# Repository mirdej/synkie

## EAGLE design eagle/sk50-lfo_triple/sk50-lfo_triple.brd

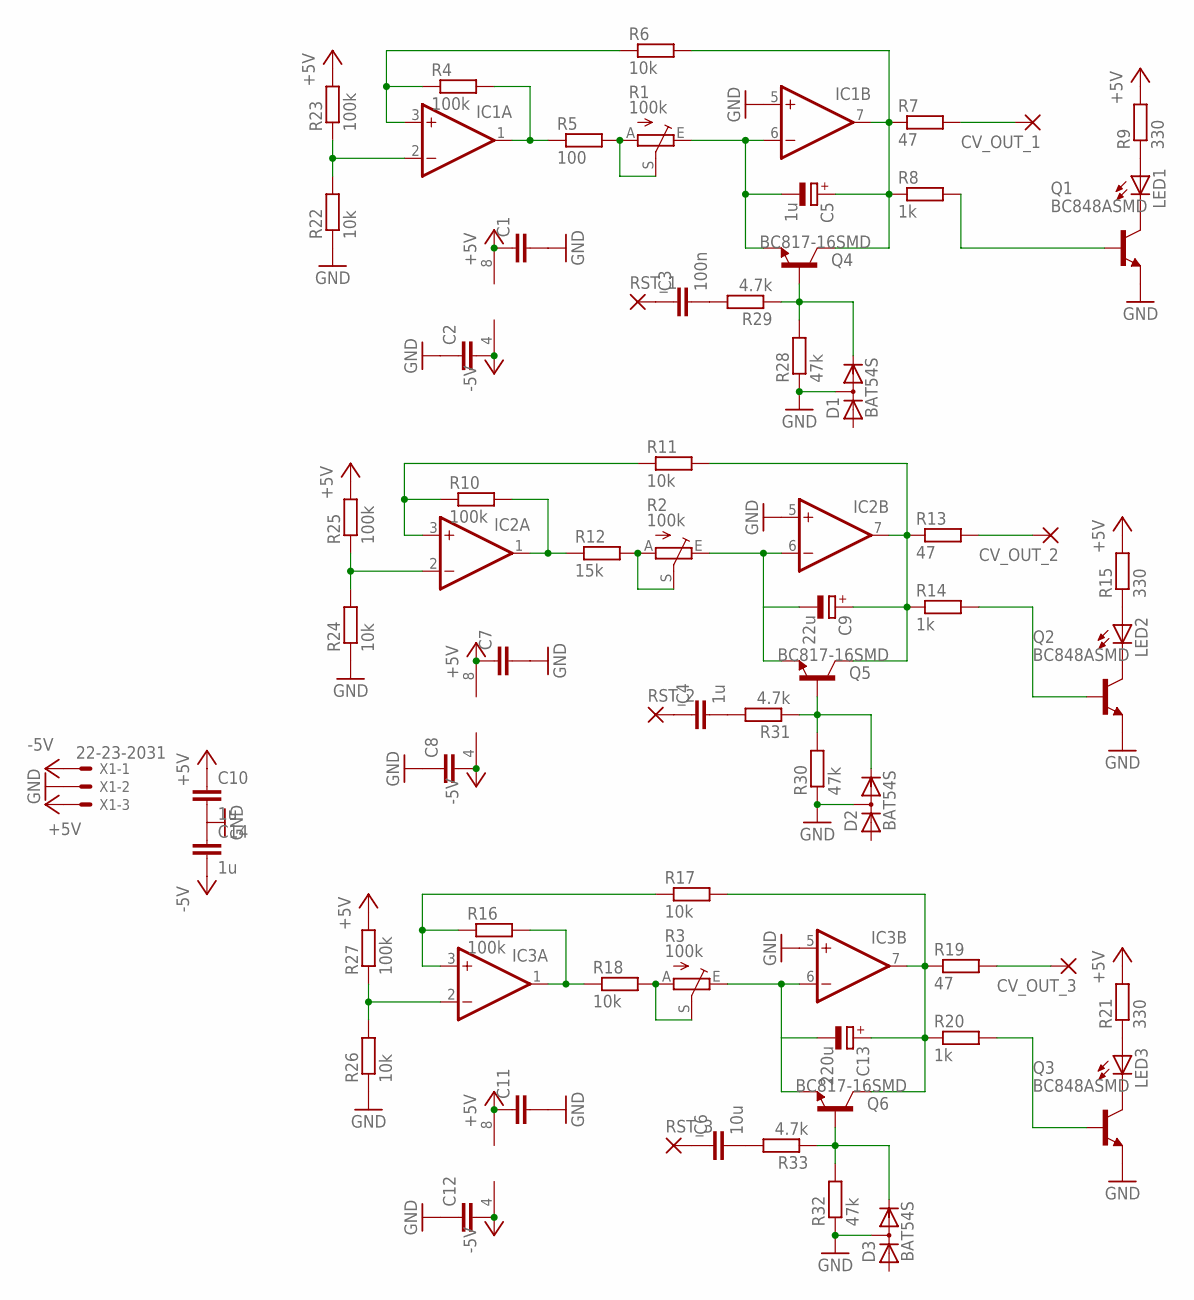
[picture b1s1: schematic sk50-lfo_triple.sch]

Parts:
C1, C2, C7, C8, C11, C12: C-EUC1206; C1206
C3: 100n; C1206
C4, C10, C14: 1u; C1206
C5: 1u; E2,5-5
C6: 10u; C1206
C9: 22u; E2,5-5
C13: 220u; E2,5-5
CV_OUT_1, CV_OUT_2, CV_OUT_3: 3,17/1,1
D1, D2, D3: BAT54S; SOT23
IC1, IC2, IC3: 2AMP_P8+4D; SO08
LED1, LED2, LED3: LED3MM
Q1, Q2, Q3: BC848ASMD; SOT23
Q4, Q5, Q6: BC817-16SMD; SOT23-BEC
R1, R2, R3: 100k; CIP20C-6MM
R4, R10, R16, R23, R25, R27: 100k; R1206
R5: 100; R1206
R6, R11, R17, R18, R22, R24, R26: 10k; R1206
R7, R13, R19: 47; R1206
R8, R14, R20: 1k; R1206
R9, R15, R21: 330; R1206
R12: 15k; R1206
R28, R30, R32: 47k; R1206
R29, R31, R33: 4.7k; R1206
RST_1, RST_2, RST_3: 3,17/1,1
X1: 22-23-2031

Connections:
+5V: C1.1, C7.1, C10.1, C11.1, IC1.8 (V+), IC2.8 (V+), IC3.8 (V+), R9.2, R15.2, R21.2, R23.2, R25.2, R27.2, X1.3
-5V: C2.2, C8.2, C12.2, C14.2, IC1.4 (V-), IC2.4 (V-), IC3.4 (V-), X1.1
GND: C1.2, C2.1, C7.2, C8.1, C10.2, C11.2, C12.1, C14.1, D1.3 (AC), D2.3 (AC), D3.3 (AC), IC1.5 (+IN), IC2.5 (+IN), IC3.5 (+IN), Q1.2 (E), Q2.2 (E), Q3.2 (E), R22.1, R24.1, R26.1, R28.1, R30.1, R32.1, X1.2
unnamed: IC1.3 (+IN), R4.1, R6.1
unnamed: IC1.1 (OUT), R4.2, R5.1
unnamed: R1.A, R1.S, R5.2
unnamed: C5.-, IC1.6 (-IN), Q4.E, R1.E
unnamed: C5.+, IC1.7 (OUT), Q4.C, R6.2, R7.1, R8.1
unnamed: LED2.A, R15.1
unnamed: CV_OUT_1.1, R7.2
unnamed: Q1.1 (B), R8.2
unnamed: LED1.A, R9.1
unnamed: LED1.K (C), Q1.3 (C)
unnamed: IC2.3 (+IN), R10.1, R11.1
unnamed: IC2.1 (OUT), R10.2, R12.1
unnamed: R2.A, R2.S, R12.2
unnamed: C9.-, IC2.6 (-IN), Q5.E, R2.E
unnamed: C9.+, IC2.7 (OUT), Q5.C, R11.2, R13.1, R14.1
unnamed: LED2.K (C), Q2.3 (C)
unnamed: CV_OUT_2.1, R13.2
unnamed: Q2.1 (B), R14.2
unnamed: LED3.A, R21.1
unnamed: LED3.K (C), Q3.3 (C)
unnamed: IC3.3 (+IN), R16.1, R17.1
unnamed: IC3.1 (OUT), R16.2, R18.1
unnamed: R3.A, R3.S, R18.2
unnamed: C13.-, IC3.6 (-IN), Q6.E, R3.E
unnamed: C13.+, IC3.7 (OUT), Q6.C, R17.2, R19.1, R20.1
unnamed: Q3.1 (B), R20.2
unnamed: CV_OUT_3.1, R19.2
unnamed: IC1.2 (-IN), R22.2, R23.1
unnamed: IC2.2 (-IN), R24.2, R25.1
unnamed: IC3.2 (-IN), R26.2, R27.1
unnamed: C3.2, R29.2
unnamed: C3.1, RST_1.1
unnamed: D2.2 (C), Q5.B, R30.2, R31.1
unnamed: D1.2 (C), Q4.B, R28.2, R29.1
unnamed: C4.2, R31.2
unnamed: C6.2, R33.2
unnamed: C4.1, RST_2.1
unnamed: C6.1, RST_3.1
unnamed: D3.2 (C), Q6.B, R32.2, R33.1

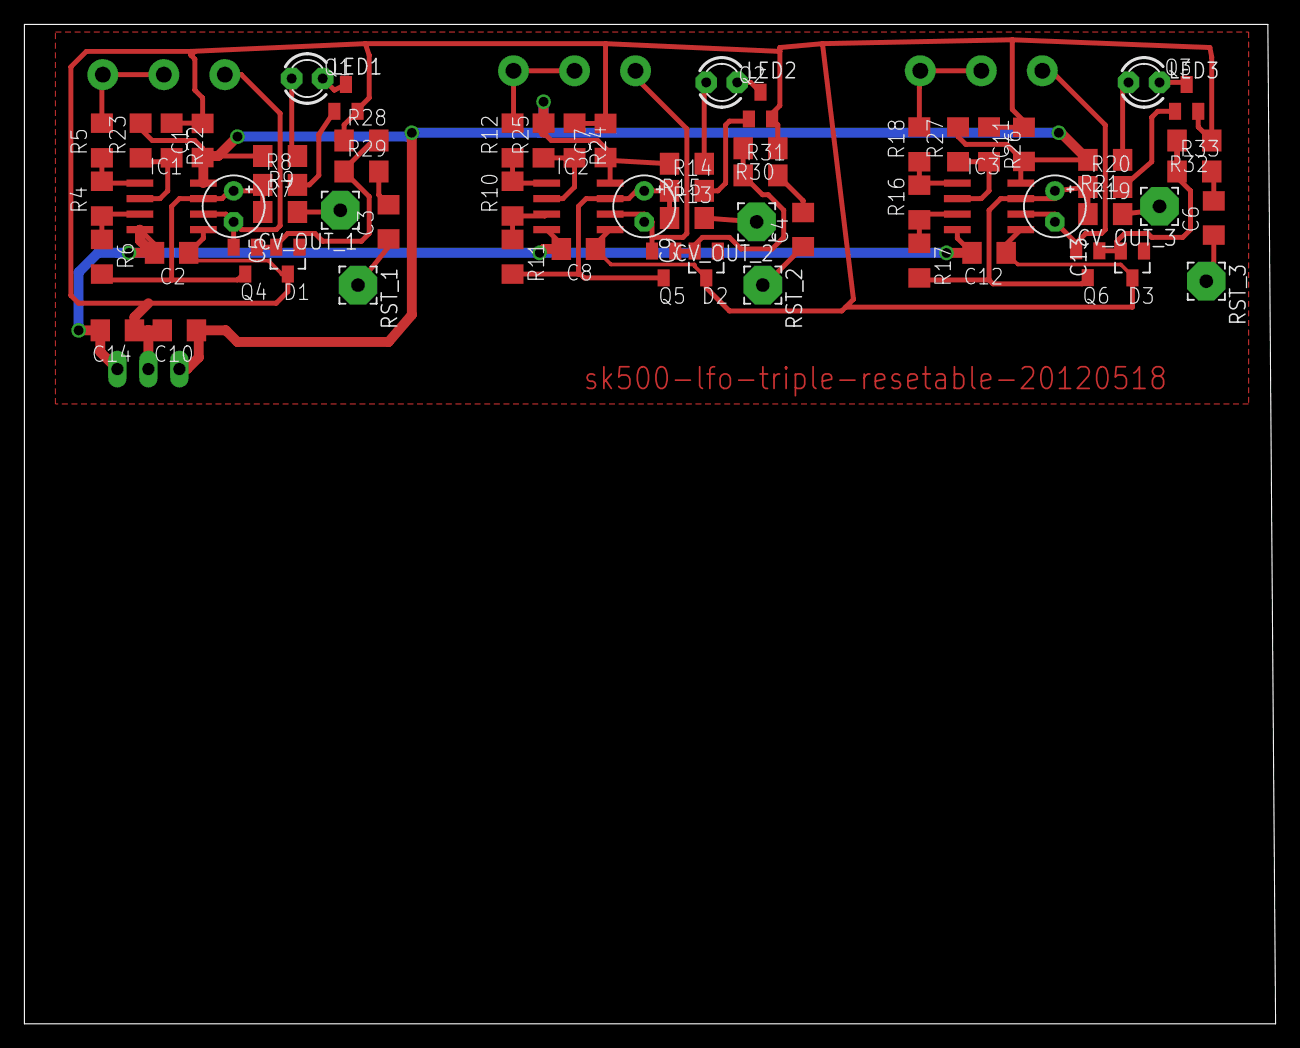
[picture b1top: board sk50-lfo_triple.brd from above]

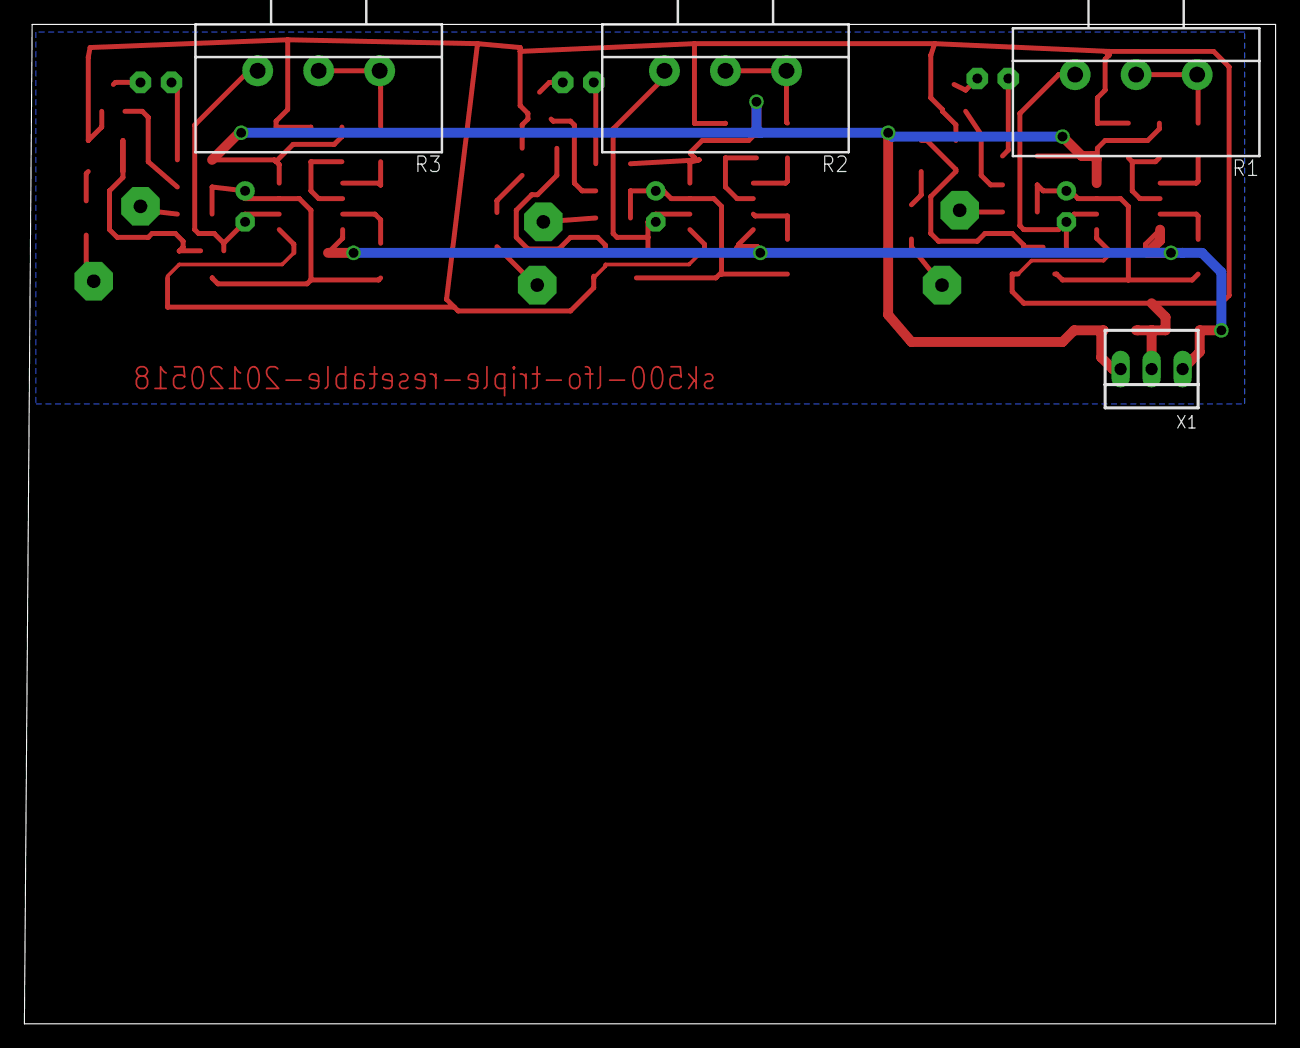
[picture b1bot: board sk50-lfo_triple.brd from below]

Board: 2 copper layers, 102.5 x 81.9 mm, 69 parts (4 on the bottom side), 42 nets.

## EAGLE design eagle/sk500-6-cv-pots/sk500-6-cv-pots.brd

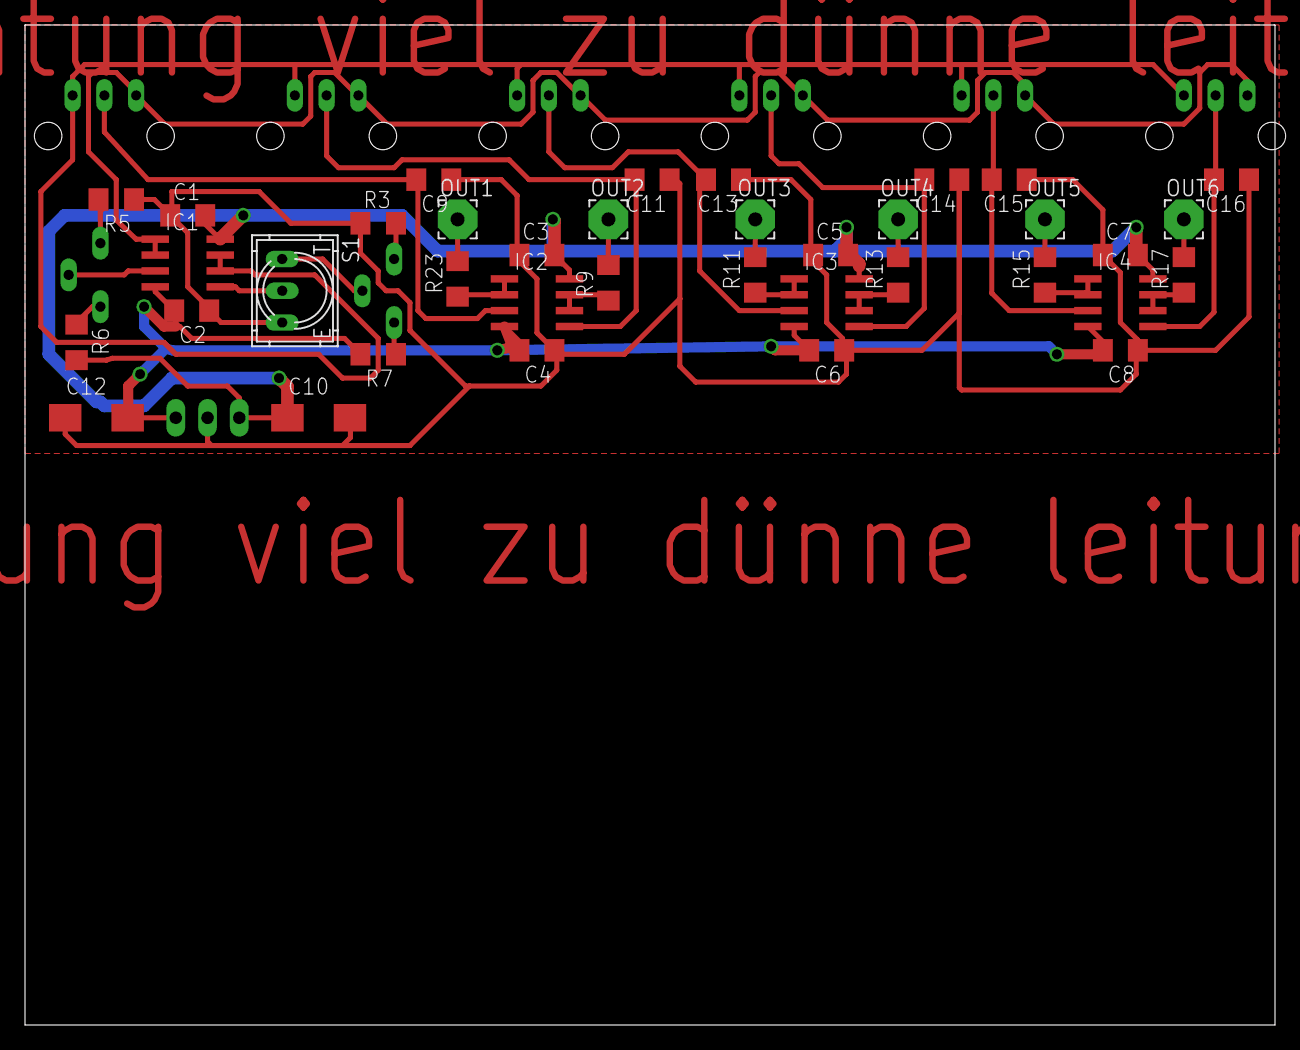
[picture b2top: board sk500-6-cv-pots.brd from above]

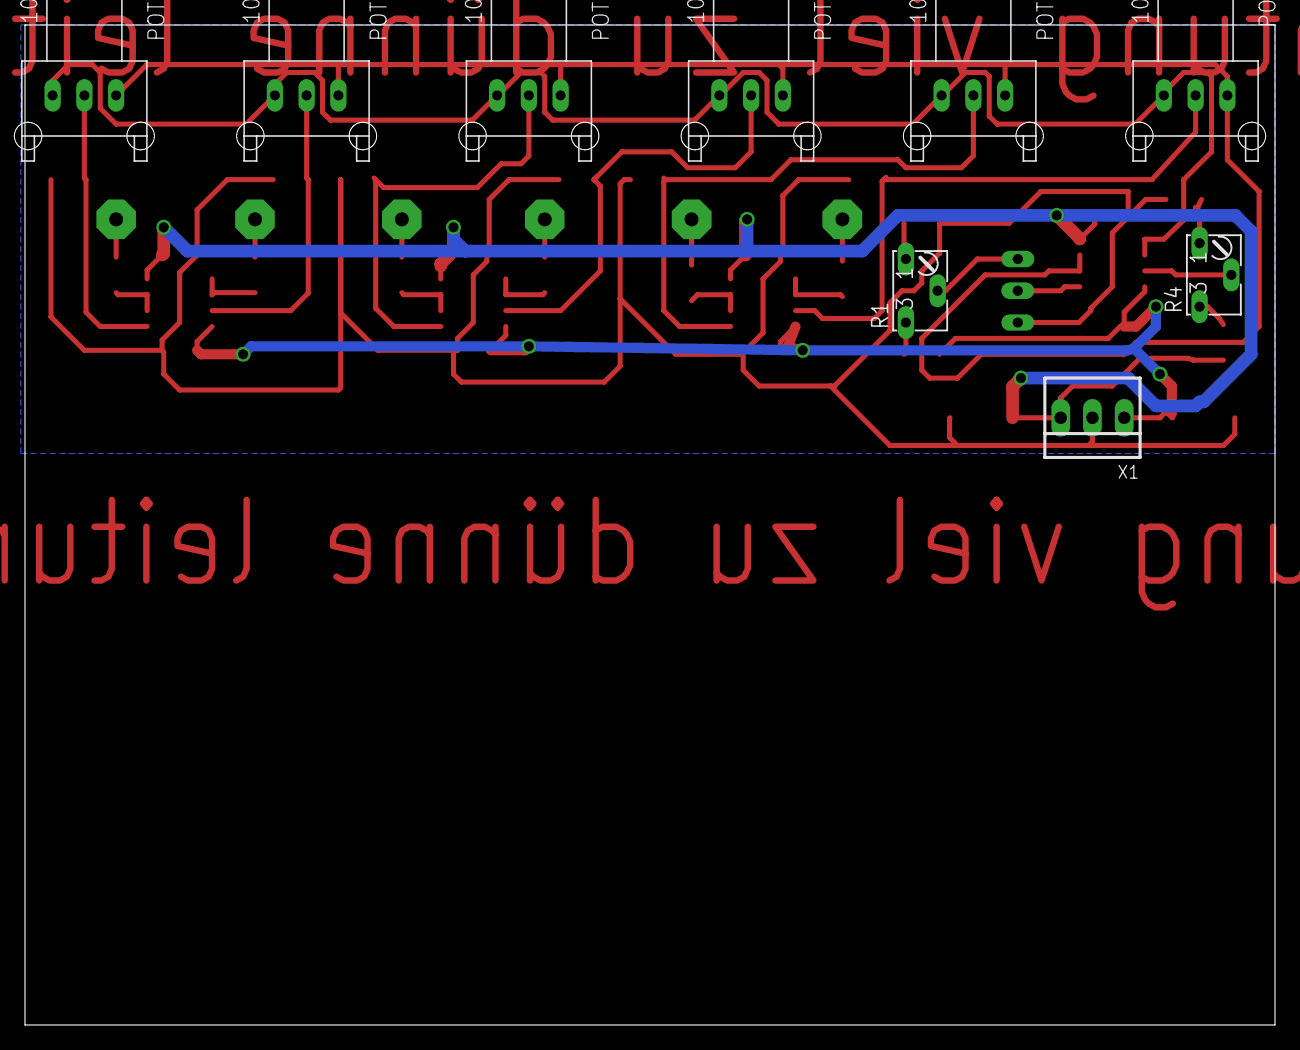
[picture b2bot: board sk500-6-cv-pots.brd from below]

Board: 2 copper layers, 100.0 x 80.0 mm, 46 parts (9 on the bottom side), 30 nets.

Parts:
C1, C2, C3, C4, C5, C6, C7, C8, C9, C11, C13, C14, C15, C16: C1206
C10, C12: CT6032
IC1, IC2, IC3, IC4: LM833D; SO08
OUT1, OUT2, OUT3, OUT4, OUT5, OUT6: 3,17/1,1
POT10K, POT10K1, POT10K2, POT10K3, POT10K4, POT10K5: 10k; ALPS_RK09K111_H
R1, R4: 500; B64W
R3, R5: 330; R1206
R6, R7: 1k6; R1206
R9, R11, R13, R15, R17, R23: 75; R1206
S1: 9077-1
X1: 22-23-2031

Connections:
+5V: C1.2, C3.2, C5.2, C7.2, C10.+, IC1.8, IC2.8, IC3.8, IC4.8, R6.2, X1.3
-5V: C2.2, C4.2, C6.2, C8.2, C12.-, IC1.4, IC2.4, IC3.4, IC4.4, R7.2, X1.1
GND: C1.1, C2.1, C3.1, C4.1, C5.1, C6.1, C7.1, C8.1, C9.1, C10.-, C11.1, C12.+, C13.1, C14.1, C15.1, C16.1, R3.1, R5.1, S1.3, X1.2
unnamed: IC1.5, S1.2
unnamed: C9.2, IC2.3, POT10K.2
unnamed: R1.A, R3.2
unnamed: R1.E, R7.1
unnamed: R1.S, S1.1
unnamed: R4.A, R5.2
unnamed: R4.E, R6.1
unnamed: IC1.3, R4.S
unnamed: IC1.1, IC1.2, POT10K.3, POT10K1.3, POT10K2.3, POT10K3.3, POT10K4.3, POT10K5.3
unnamed: IC2.1, IC2.2, R23.1
unnamed: OUT2.1, R9.2
unnamed: OUT3.1, R11.2
unnamed: IC2.6, IC2.7, R9.1
unnamed: IC3.1, IC3.2, R11.1
unnamed: OUT4.1, R13.2
unnamed: OUT1.1, R23.2
unnamed: IC3.6, IC3.7, R13.1
unnamed: C11.2, IC2.5, POT10K1.2
unnamed: C13.2, IC3.3, POT10K2.2
unnamed: OUT5.1, R15.2
unnamed: C14.2, IC3.5, POT10K3.2
unnamed: IC4.1, IC4.2, R15.1
unnamed: IC1.6, IC1.7, POT10K.1, POT10K1.1, POT10K2.1, POT10K3.1, POT10K4.1, POT10K5.1
unnamed: OUT6.1, R17.2
unnamed: IC4.6, IC4.7, R17.1
unnamed: C15.2, IC4.3, POT10K4.2
unnamed: C16.2, IC4.5, POT10K5.2

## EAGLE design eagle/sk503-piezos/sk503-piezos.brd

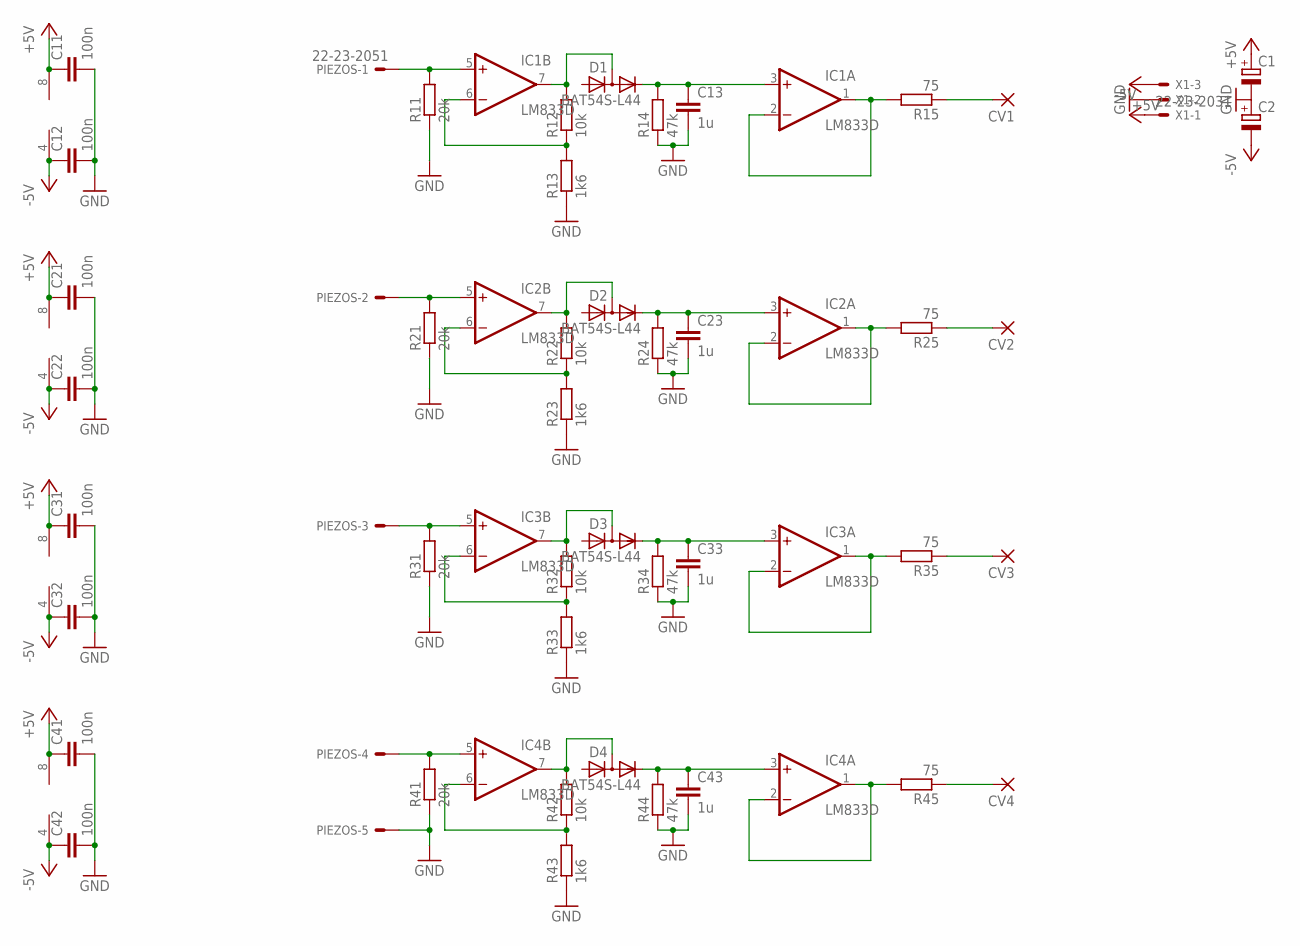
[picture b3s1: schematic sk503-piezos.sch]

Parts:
C1, C2: CPOL-EUCT6032; CT6032
C11, C12, C21, C22, C31, C32, C41, C42: 100n; C1206
C13, C23, C33, C43: 1u; C1206
CV1, CV2, CV3, CV4: 3,17/1,1
D1, D2, D3, D4: BAT54S-L44; SOT23
IC1, IC2, IC3, IC4: LM833D; SO08
PIEZOS: 22-23-2051
R11, R21, R31, R41: 20k; R1206
R12, R22, R32, R42: 10k; R1206
R13, R23, R33, R43: 1k6; R1206
R14, R24, R34, R44: 47k; R1206
R15, R25, R35, R45: 75; R1206
X1: 22-23-2031

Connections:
+5V: C1.+, C11.1, C21.1, C31.1, C41.1, IC1.8 (V+), IC2.8 (V+), IC3.8 (V+), IC4.8 (V+), X1.3
-5V: C2.-, C12.1, C22.1, C32.1, C42.1, IC1.4 (V-), IC2.4 (V-), IC3.4 (V-), IC4.4 (V-), X1.1
GND: C1.-, C2.+, C11.2, C12.2, C13.2, C21.2, C22.2, C23.2, C31.2, C32.2, C33.2, C41.2, C42.2, C43.2, PIEZOS.5, R11.1, R13.1, R14.1, R21.1, R23.1, R24.1, R31.1, R33.1, R34.1, R41.1, R43.1, R44.1, X1.2
unnamed: IC1.5 (+IN), PIEZOS.1, R11.2
unnamed: D1.3 (AC), IC1.7 (OUT), R12.2
unnamed: IC1.6 (-IN), R12.1, R13.2
unnamed: IC1.1 (OUT), IC1.2 (-IN), R15.2
unnamed: CV1.1, R15.1
unnamed: IC2.5 (+IN), PIEZOS.2, R21.2
unnamed: IC2.6 (-IN), R22.1, R23.2
unnamed: C13.1, D1.2 (C), IC1.3 (+IN), R14.2
unnamed: IC2.1 (OUT), IC2.2 (-IN), R25.2
unnamed: CV2.1, R25.1
unnamed: C23.1, D2.2 (C), IC2.3 (+IN), R24.2
unnamed: IC3.5 (+IN), PIEZOS.3, R31.2
unnamed: D3.3 (AC), IC3.7 (OUT), R32.2
unnamed: IC3.6 (-IN), R32.1, R33.2
unnamed: IC3.1 (OUT), IC3.2 (-IN), R35.2
unnamed: CV3.1, R35.1
unnamed: C33.1, D3.2 (C), IC3.3 (+IN), R34.2
unnamed: IC4.5 (+IN), PIEZOS.4, R41.2
unnamed: IC4.6 (-IN), R42.1, R43.2
unnamed: IC4.1 (OUT), IC4.2 (-IN), R45.2
unnamed: CV4.1, R45.1
unnamed: C43.1, D4.2 (C), IC4.3 (+IN), R44.2
unnamed: D2.3 (AC), IC2.7 (OUT), R22.2
unnamed: D4.3 (AC), IC4.7 (OUT), R42.2

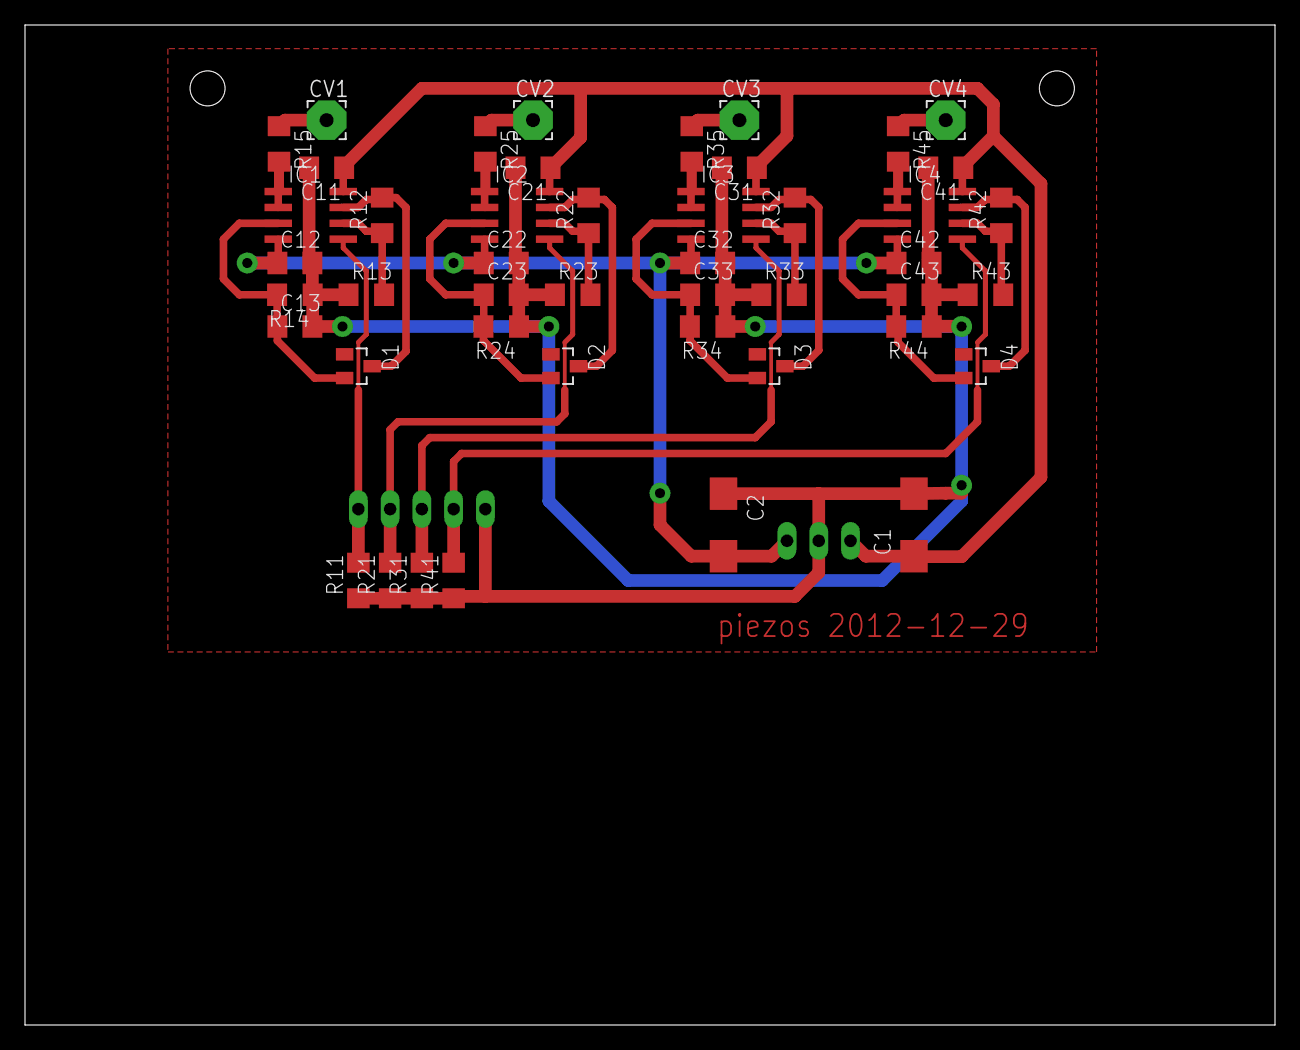
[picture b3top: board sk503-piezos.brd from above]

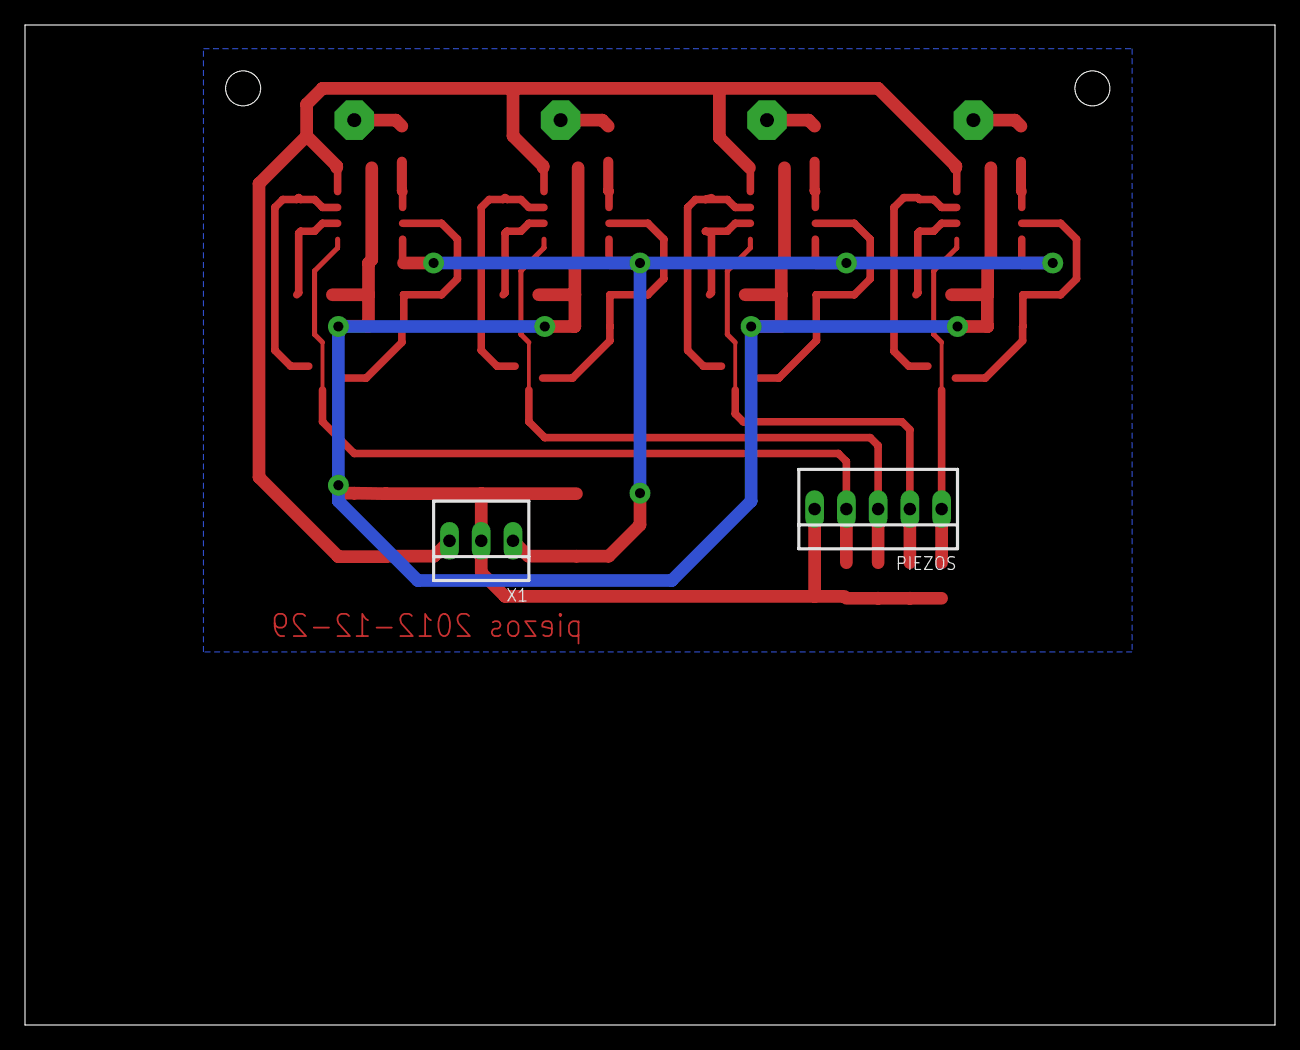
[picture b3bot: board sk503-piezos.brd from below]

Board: 2 copper layers, 100.0 x 80.0 mm, 48 parts (2 on the bottom side), 27 nets.

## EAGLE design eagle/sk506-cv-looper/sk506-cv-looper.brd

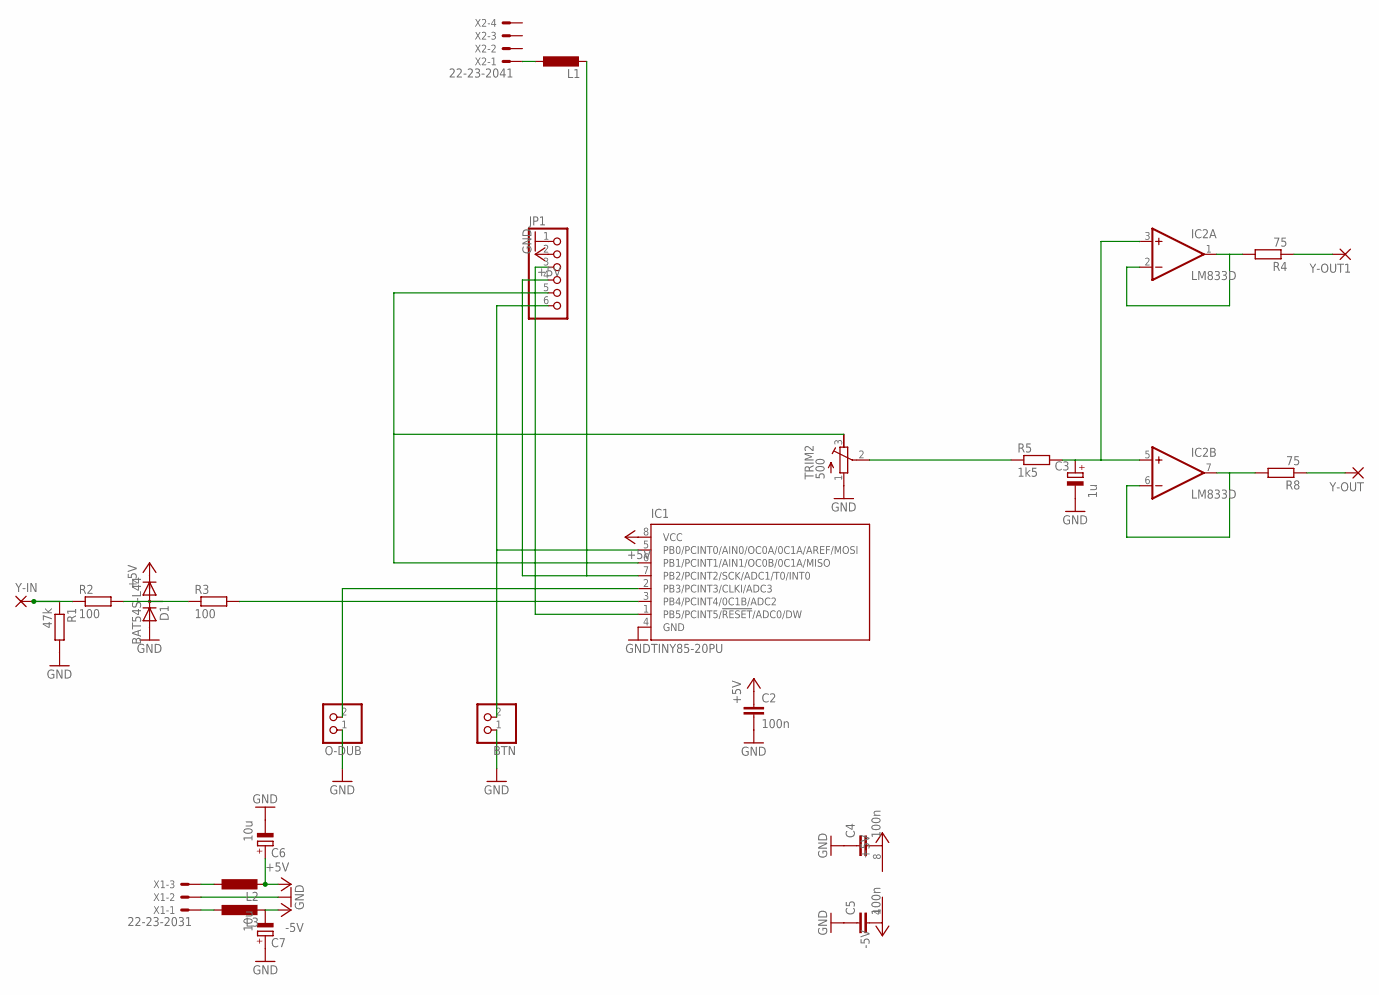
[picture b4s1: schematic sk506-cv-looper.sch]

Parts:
BTN: PINHD-1X2; 1X02
C2: 100n; C1206
C3: 1u; CT3528
C4, C5: 100n; C0603
C6, C7: 10u; CT3528
D1: BAT54S-L44; SOT23
IC1: TINY85-20PU; DIL08; MPN ATTINY13-20PU
IC2: LM833D; SO08
JP1: PINHD-1X6; 1X06
L1, L2, L3: L-EUL3216C; L3216C
O-DUB: PINHD-1X2; 1X02
R1: 47k; R1206
R2, R3: 100; R1206
R4, R8: 75; R1206
R5: 1k5; R1206
TRIM2: 500; RTRIM64Y
X1: 22-23-2031
X2: 22-23-2041
Y-IN: 3,17/1,1
Y-OUT, Y-OUT1: 3,17/1,1

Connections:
+5V: C2.1, C4.2, C6.+, D1.2 (C), IC1.8 (VCC), IC2.8 (V+), JP1.2, L2.2
-5V: C5.2, C7.-, IC2.4 (V-), L3.2
GND: BTN.1, C2.2, C3.-, C4.1, C5.1, C6.-, C7.+, D1.1 (A), IC1.4 (GND), JP1.1, O-DUB.1, R1.2, TRIM2.1 (E), X1.2
unnamed: IC1.1 (PB5/PCINT5/!RESET!/ADC0/DW), JP1.3
unnamed: IC1.7 (PB2/PCINT2/SCK/ADC1/T0/INT0), JP1.4, L1.2
unnamed: IC1.6 (PB1/PCINT1/AIN1/OC0B/0C1A/MISO), JP1.5, TRIM2.3 (A)
unnamed: BTN.2, IC1.5 (PB0/PCINT0/AIN0/OC0A/0C1A/AREF/MOSI), JP1.6
unnamed: R1.1, R2.1, Y-IN.1
unnamed: D1.3 (AC), R2.2, R3.1
unnamed: IC1.3 (PB4/PCINT4/0C1B/ADC2), R3.2
unnamed: IC1.2 (PB3/PCINT3/CLKI/ADC3), O-DUB.2
unnamed: C3.+, IC2.3 (+IN), IC2.5 (+IN), R5.2
unnamed: L1.1, X2.1
unnamed: L2.1, X1.3
unnamed: R8.1, Y-OUT.1
unnamed: R5.1, TRIM2.2 (S)
unnamed: IC2.6 (-IN), IC2.7 (OUT), R8.2
unnamed: L3.1, X1.1
unnamed: IC2.2 (-IN), R4.2
unnamed: R4.1, Y-OUT1.1

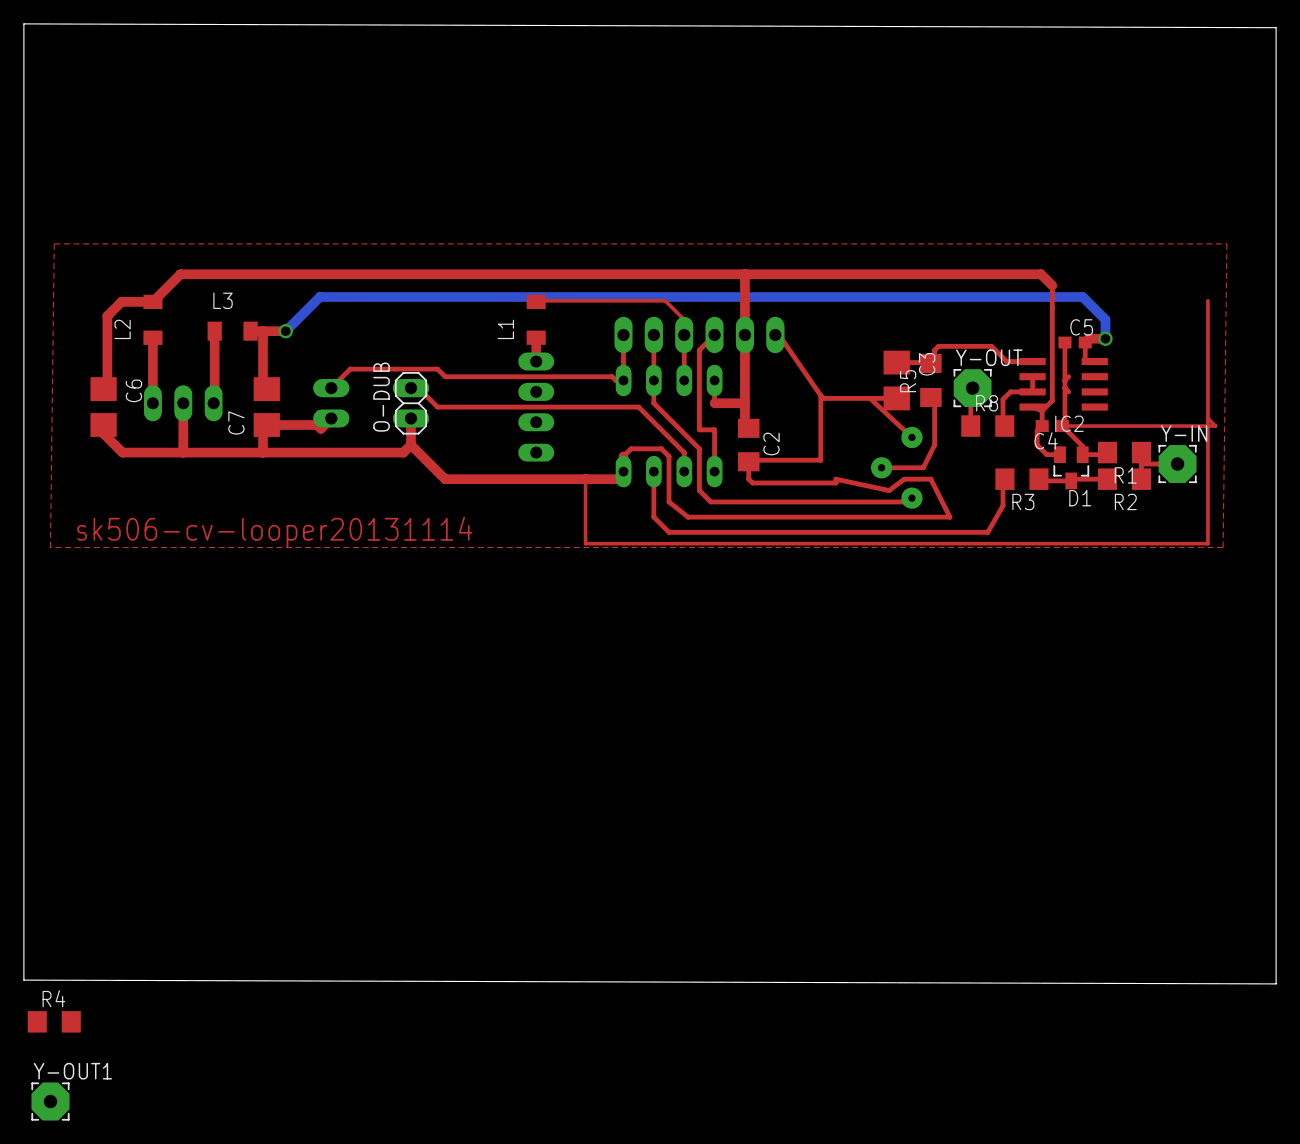
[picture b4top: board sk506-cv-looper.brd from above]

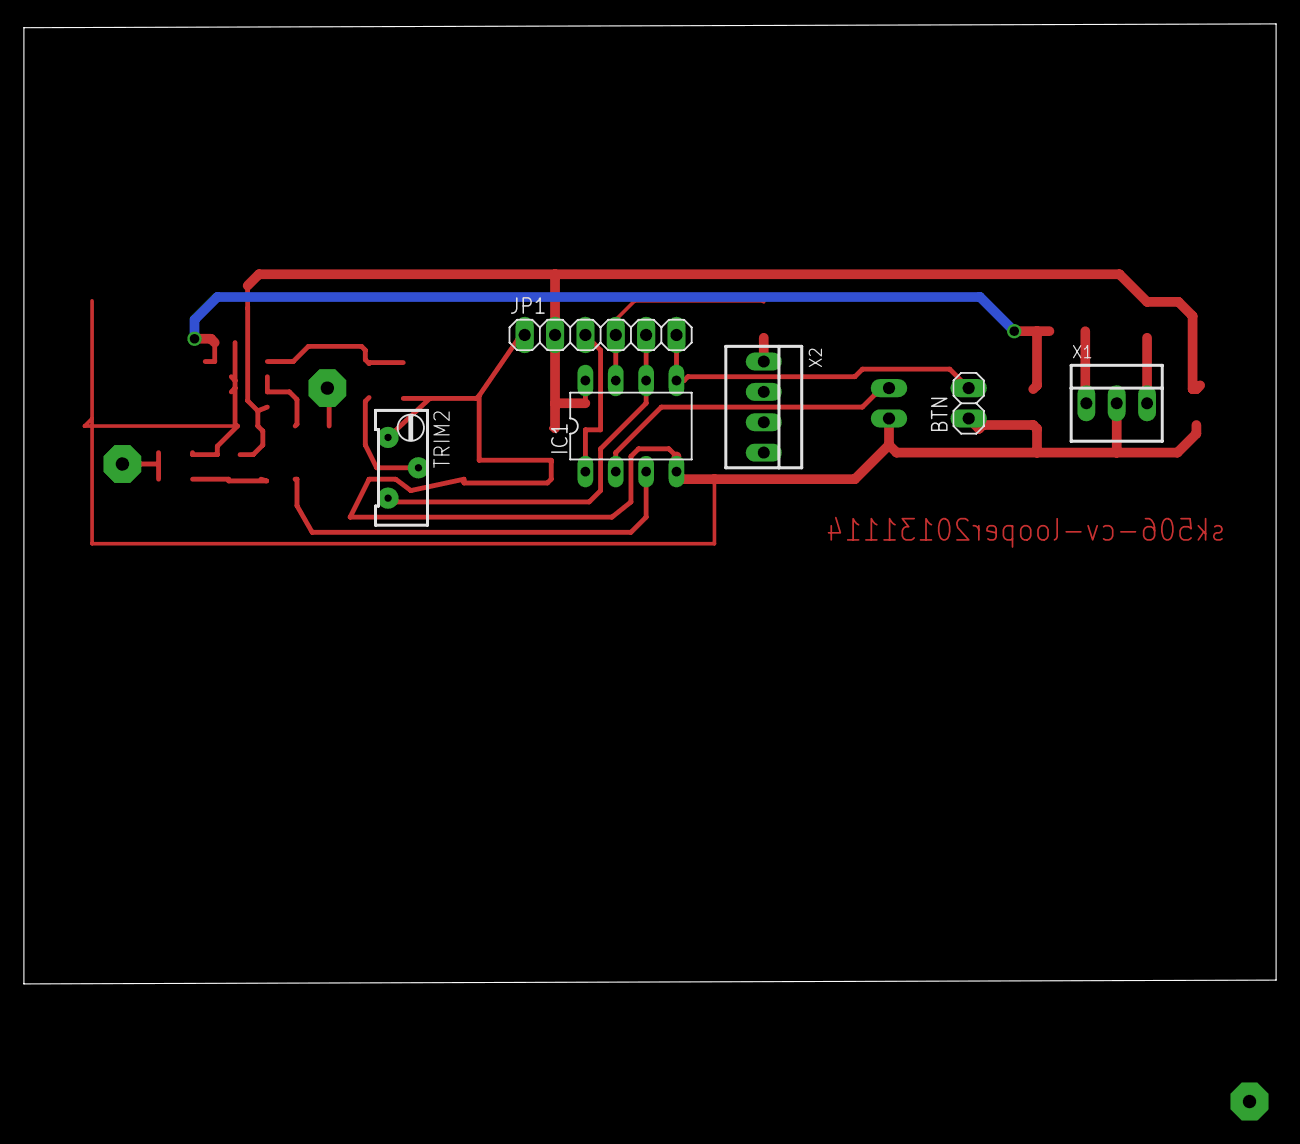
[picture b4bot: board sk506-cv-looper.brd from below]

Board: 2 copper layers, 104.8 x 80.3 mm, 27 parts (6 on the bottom side), 20 nets.

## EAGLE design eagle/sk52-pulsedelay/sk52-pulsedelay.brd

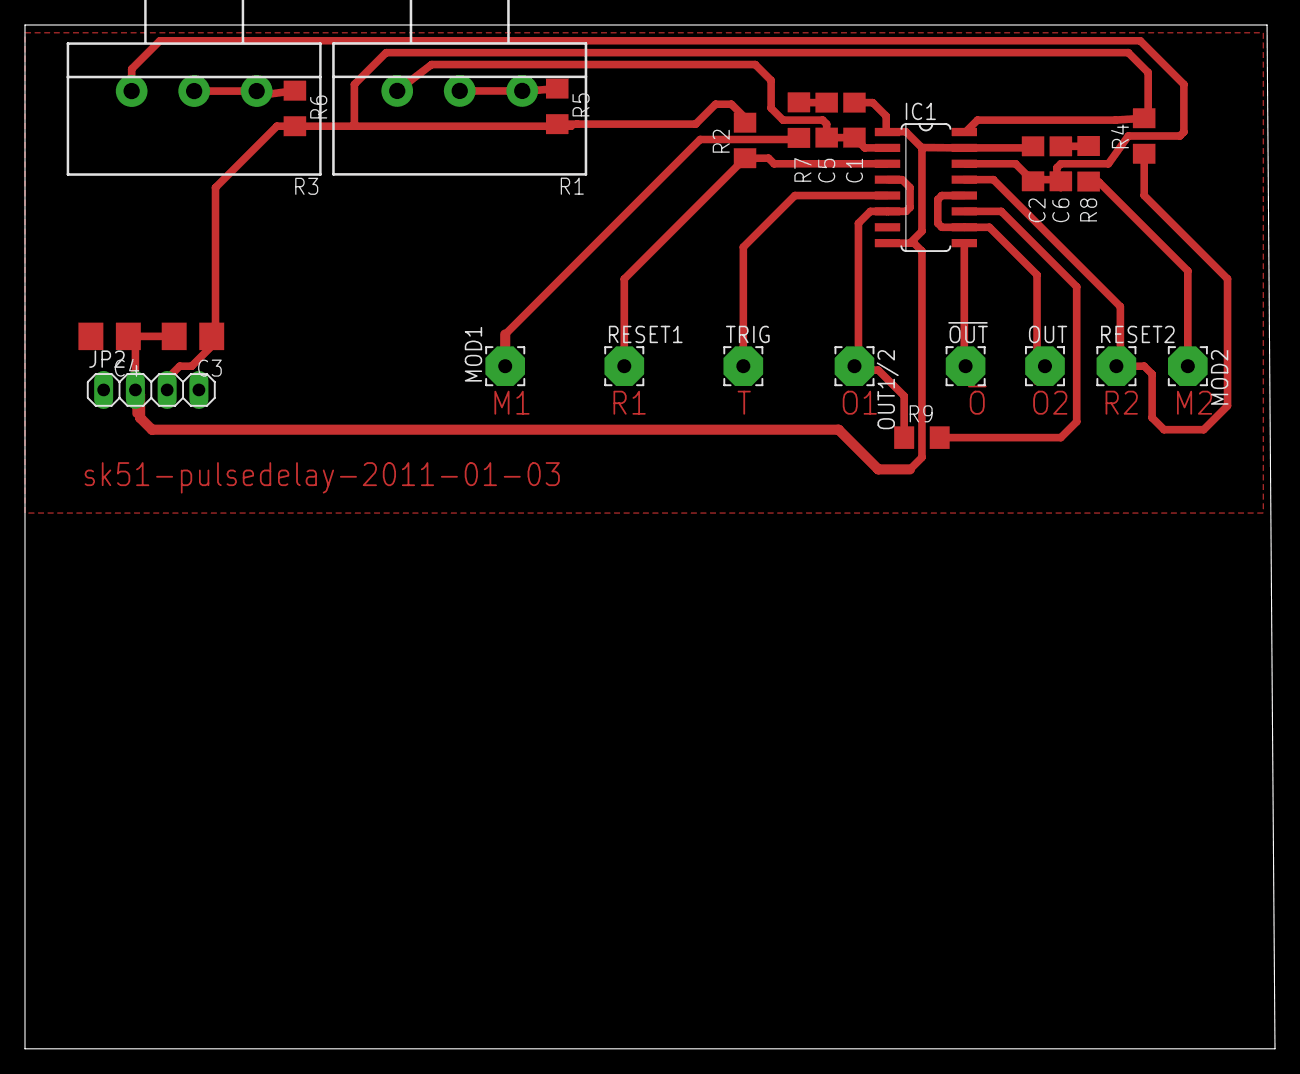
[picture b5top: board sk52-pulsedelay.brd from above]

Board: 2 copper layers, 100.0 x 81.9 mm, 25 parts (0 on the bottom side), 18 nets.

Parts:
!OUT: 3,17/1,1
C1, C2: 1n; C1206
C3, C4: 2u2tantal; CT3528
C5, C6: 220n; C1206
IC1: 4538D; SO16
JP2: 1X04
MOD1, MOD2: 3,17/1,1
OUT, OUT1/2: 3,17/1,1
R1, R3: 100k; CIP20C-6MM
R2, R4: 100k; R1206
R5, R6, R9: 0; R1206
R7, R8: 10k; R1206
RESET1, RESET2: 3,17/1,1
TRIG: 3,17/1,1

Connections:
+5V: C3.+, IC1.16, JP2.3, R2.2, R4.2, R5.2, R6.2
-5V: C4.-, JP2.1
GND: C1.1, C2.1, C3.-, C4.+, IC1.1, IC1.8, IC1.15, JP2.2
unnamed: IC1.3, R2.1, RESET1.1
unnamed: C6.1, R8.1
unnamed: IC1.10, IC1.12, OUT.1
unnamed: IC1.11, R9.2
unnamed: R1.A, R1.S, R5.1
unnamed: C1.2, C5.2, IC1.2, R1.E
unnamed: IC1.5, TRIG.1
unnamed: C5.1, R7.1
unnamed: R3.A, R3.S, R6.1
unnamed: MOD1.1, R7.2
unnamed: IC1.4, IC1.6, OUT1/2.1, R9.1
unnamed: IC1.13, R4.1, RESET2.1
unnamed: !OUT.1, IC1.9
unnamed: C2.2, C6.2, IC1.14, R3.E
unnamed: MOD2.1, R8.2
